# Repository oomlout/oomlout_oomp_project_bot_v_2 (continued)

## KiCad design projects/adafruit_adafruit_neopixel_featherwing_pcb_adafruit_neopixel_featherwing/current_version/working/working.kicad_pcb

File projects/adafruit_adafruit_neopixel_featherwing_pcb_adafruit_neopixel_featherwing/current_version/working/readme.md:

# adafruit_neopixel_featherwing_pcb
 
## summary 
* id: adafruit_adafruit_neopixel_featherwing_pcb_adafruit_neopixel_featherwing
* user: adafruit
* name: adafruit_neopixel_featherwing_pcb
* board: adafruit_neopixel_featherwing
* repo: https://github.com/adafruit/Adafruit-NeoPixel-FeatherWing-PCB

* src_file_repo_sch: 
* src_file_repo_sch_link: https://github.com/adafruit/Adafruit-NeoPixel-FeatherWing-PCB/tree/master/
* full details link: https://github.com/oomlout/oomlout_oomp_project_bot_v_2/tree/main/projects/adafruit_adafruit_neopixel_featherwing_pcb_adafruit_neopixel_featherwing/current_version/working  

## schematic  
  
[schematic (pdf)](working_schematic.pdf) 

## pcb  

[board (pdf)](working.pdf)  

## working_bom
| Id | Designator | Footprint | Quantity | Designation | Supplier and ref |  | None | 
| --- | --- | --- | --- | --- | --- | --- | --- | 
| 1 | LED6,LED19,LED32,LED26,LED23,LED8,LED9,LED12,LED11,LED28,LED2,LED31,LED25,LED18,LED21,LED5,LED24,LED20,LED16,LED29,LED1,LED4,LED14,LED27,LED13,LED10,LED15,LED17,LED30,LED3,LED22,LED7 | LED3535 | 32 | WS2812B3535 |  |  | [''] | 
| 2 | C3,C2,C1,C4,C5 | 0805-NO | 5 | 10uF |  |  | [''] | 
| 3 | JP3,JP1 | 1X01_ROUND | 2 |  |  |  | [''] | 
| 4 | FID3,FID1 | FIDUCIAL_1MM | 2 | FIDUCIAL" |  |  | [''] | 
| 5 | U$2 | PCBFEAT-REV-040 | 1 |  |  |  | [''] | 
| 6 | D1,D2 | SOD-123 | 2 | MBR120 |  |  | [''] | 
| 7 | IC2 | SOT23-5 | 1 | 74AHCT1G125DBV |  |  | [''] | 
| 8 | SW1 | BTN_KMR2_4.6X2.8 | 1 | KMR2 |  |  | [''] | 
| 9 | MS1 | FEATHERWING | 1 | FEATHERWING |  |  | [''] | 
| 10 | SJ10,SJ7,SJ2,SJ18,SJ11,SJ19,SJ9,SJ1,SJ5,SJ16,SJ12,SJ3,SJ17,SJ8,SJ14,SJ4,SJ15,SJ6,SJ13 | SOLDERJUMPER_ARROW_NOPASTE | 19 |  |  |  | [''] | 
| 11 | U$4 | ADAFRUIT_TEXT_20MM | 1 |  |  |  | [''] | 
| 12 | U$3 | FEATHERLOGO | 1 |  |  |  | [''] | 
| 13 | SJ20 | SOLDERJUMPER_CLOSEDWIRE | 1 |  |  |  | [''] | 

## bom_schematic
| Ref | Qnty | Value | Cmp name | Footprint | Description | Vendor | DNP | 
| --- | --- | --- | --- | --- | --- | --- | --- | 
| C1, C2, C3, C4, C5 | 5 | 10uF | CAP_CERAMIC0805-NOOUTLINE | working:0805-NO |  |  |  | 
| D1, D2 | 2 | MBR120 | DIODE-SCHOTTKYSOD-123 | working:SOD-123 |  |  |  | 
| FID1, FID3 | 2 | FIDUCIAL"" | FIDUCIAL{dblquote}{dblquote} | working:FIDUCIAL_1MM |  |  |  | 
| IC2 | 1 | 741G125DBV | 741G125DBV | working:SOT23-5 |  |  |  | 
| JP1, JP3 | 2 | HEADER-1X1ROUND | HEADER-1X1ROUND | working:1X01_ROUND |  |  |  | 
| LED1, LED2, LED3, LED4, LED5, LED6, LED7, LED8, LED9, LED10, LED11, LED12, LED13, LED14, LED15, LED16, LED17, LED18, LED19, LED20, LED21, LED22, LED23, LED24, LED25, LED26, LED27, LED28, LED29, LED30, LED31, LED32 | 32 | WS2812B3535 | WS2812B3535 | working:LED3535 |  |  |  | 
| MS1 | 1 | FEATHERWING | FEATHERWING | working:FEATHERWING |  |  |  | 
| SJ1, SJ2, SJ3, SJ4, SJ5, SJ6, SJ7, SJ8, SJ9, SJ10, SJ11, SJ12, SJ13, SJ14, SJ15, SJ16, SJ17, SJ18, SJ19 | 19 | SOLDERJUMPER | SOLDERJUMPER | working:SOLDERJUMPER_ARROW_NOPASTE |  |  |  | 
| SJ20 | 1 | SOLDERJUMPERCLOSED | SOLDERJUMPERCLOSED | working:SOLDERJUMPER_CLOSEDWIRE |  |  |  | 
| SW1 | 1 | KMR2 | SWITCH_TACT_SMT4.6X2.8 | working:BTN_KMR2_4.6X2.8 |  |  |  |

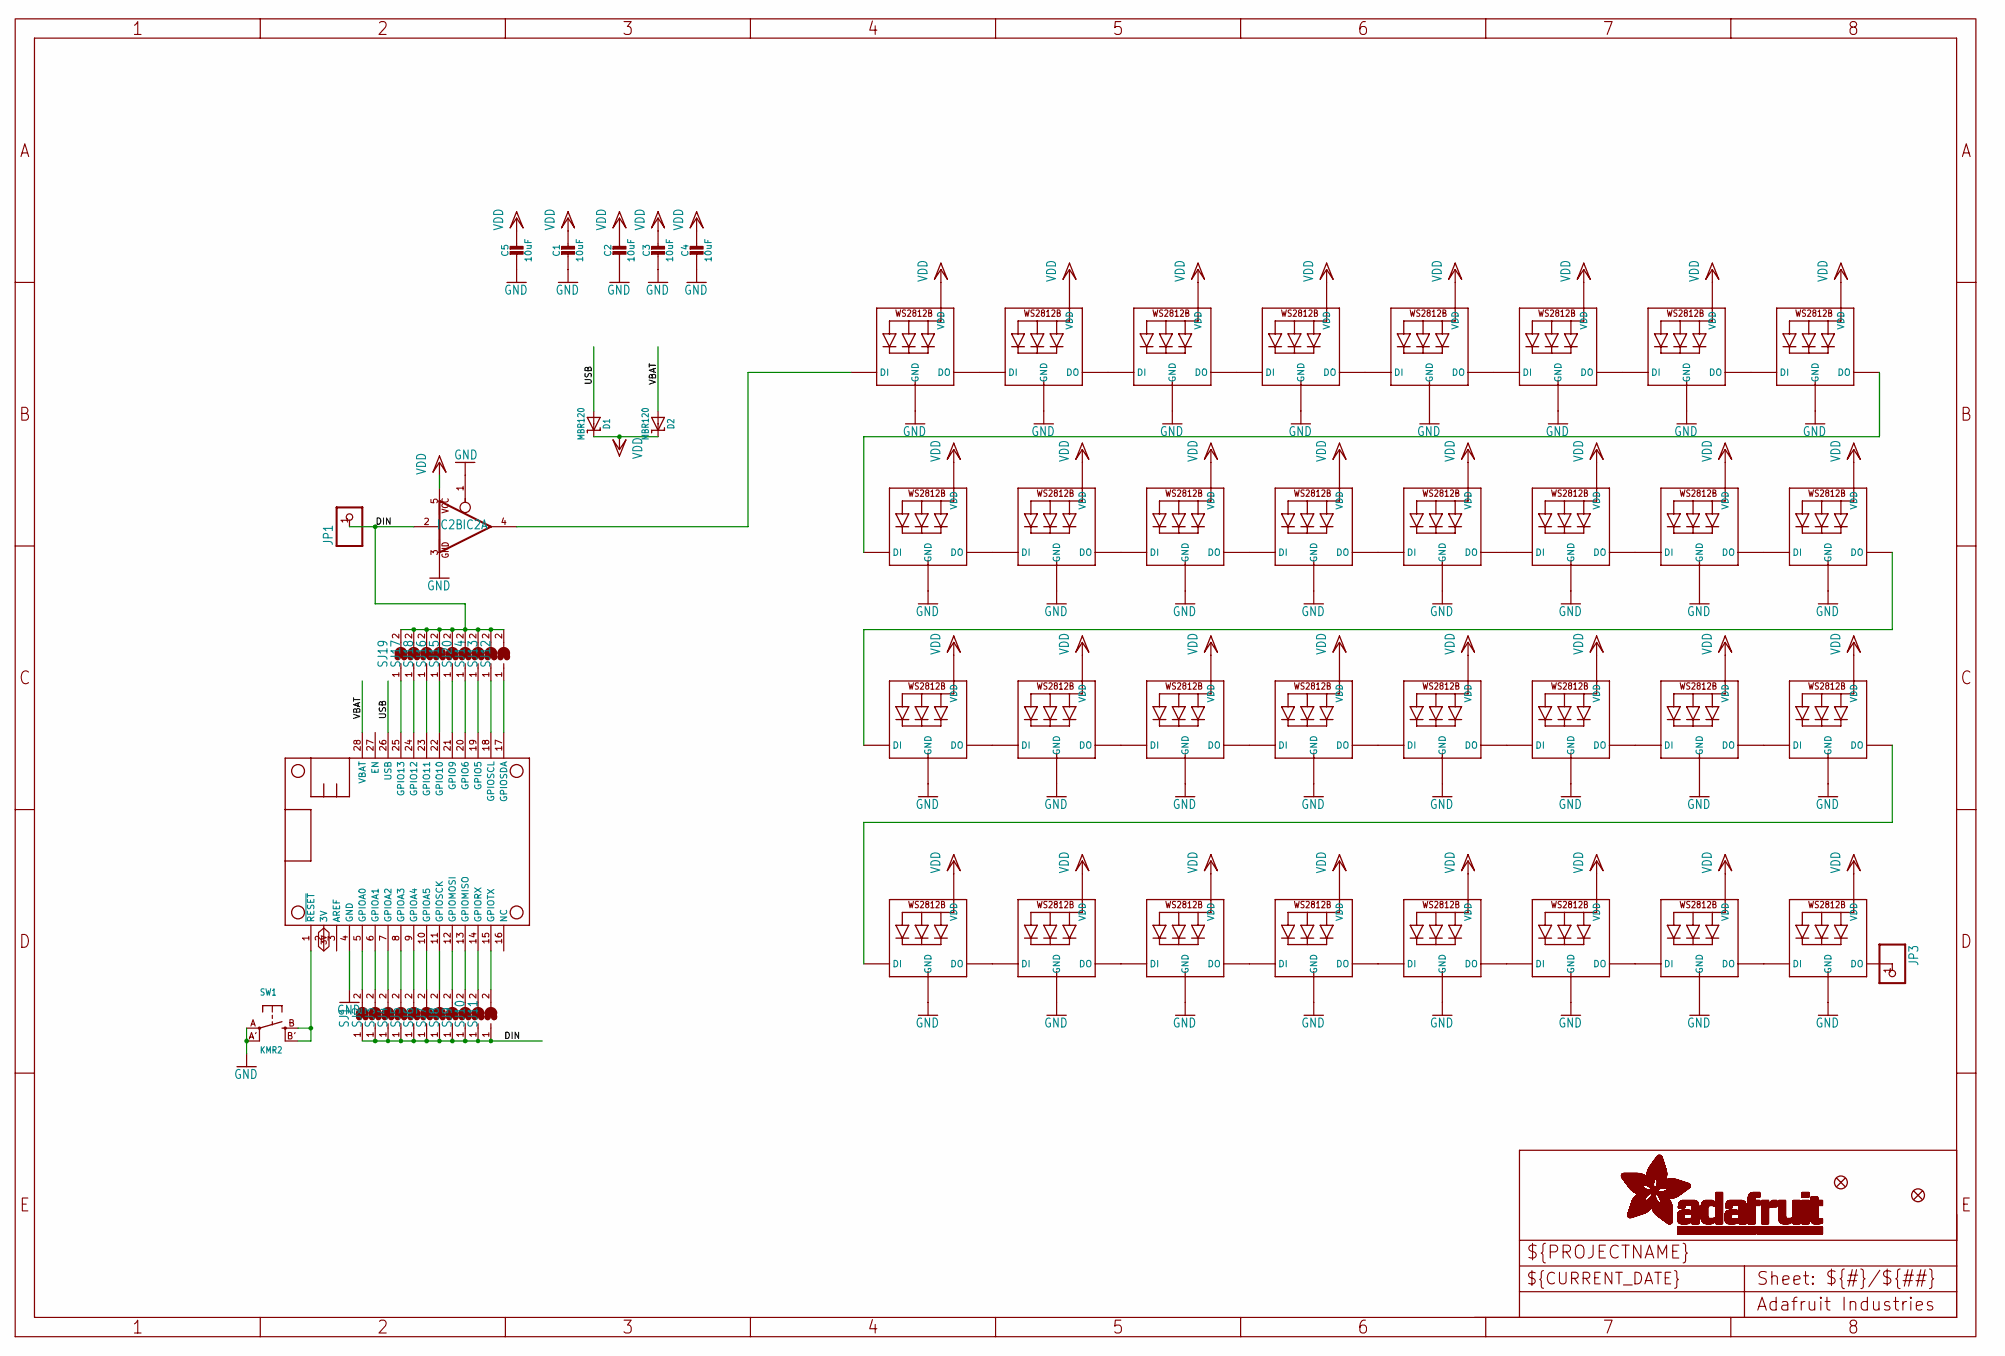
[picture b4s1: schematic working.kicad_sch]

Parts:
C1, C2, C3, C4, C5: 10uF; 0805-NO
D1, D2: MBR120; SOD-123
FID1, FID3: FIDUCIAL""; FIDUCIAL_1MM
IC2: 741G125DBV; SOT23-5
JP1, JP3: HEADER-1X1ROUND; 1X01_ROUND
LED1, LED2, LED3, LED4, LED5, LED6, LED7, LED8, LED9, LED10, LED11, LED12, LED13, LED14, LED15, LED16, LED17, LED18, LED19, LED20, LED21, LED22, LED23, LED24, LED25, LED26, LED27, LED28, LED29, LED30, LED31, LED32: WS2812B3535; LED3535
MS1: FEATHERWING
SJ1, SJ2, SJ3, SJ4, SJ5, SJ6, SJ7, SJ8, SJ9, SJ10, SJ11, SJ12, SJ13, SJ14, SJ15, SJ16, SJ17, SJ18, SJ19: SOLDERJUMPER; SOLDERJUMPER_ARROW_NOPASTE
SJ20: SOLDERJUMPERCLOSED; SOLDERJUMPER_CLOSEDWIRE
SW1: KMR2; BTN_KMR2_4.6X2.8

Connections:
D6: MS1.20 (GPIO6), SJ20.1
DIN: IC2.2 (I), JP1.1, SJ1.1, SJ2.1, SJ3.1, SJ4.1, SJ5.1, SJ6.1, SJ7.1, SJ8.1, SJ9.1, SJ10.1, SJ11.1, SJ12.2, SJ13.2, SJ14.2, SJ15.2, SJ16.2, SJ17.2, SJ18.2, SJ19.2, SJ20.2
GND: C1.2, C2.2, C3.2, C4.2, C5.2, IC2.1 (OE), IC2.3 (GND), LED1.4 (GND), LED2.4 (GND), LED3.4 (GND), LED4.4 (GND), LED5.4 (GND), LED6.4 (GND), LED7.4 (GND), LED8.4 (GND), LED9.4 (GND), LED10.4 (GND), LED11.4 (GND), LED12.4 (GND), LED13.4 (GND), LED14.4 (GND), LED15.4 (GND), LED16.4 (GND), LED17.4 (GND), LED18.4 (GND), LED19.4 (GND), LED20.4 (GND), LED21.4 (GND), LED22.4 (GND), LED23.4 (GND), LED24.4 (GND), LED25.4 (GND), LED26.4 (GND), LED27.4 (GND), LED28.4 (GND), LED29.4 (GND), LED30.4 (GND), LED31.4 (GND), LED32.4 (GND), MS1.4 (GND), SW1.A, SW1.A' (P1)
unnamed: LED19.3 (DO), LED20.1 (DI)
unnamed: LED20.3 (DO), LED21.1 (DI)
unnamed: MS1.25 (GPIO13), SJ19.1
unnamed: MS1.15 (GPIOTX), SJ11.2
unnamed: MS1.24 (GPIO12), SJ17.1
unnamed: MS1.14 (GPIORX), SJ10.2
unnamed: MS1.13 (GPIOMISO), SJ9.2
unnamed: MS1.12 (GPIOMOSI), SJ8.2
unnamed: MS1.11 (GPIOSCK), SJ7.2
unnamed: MS1.10 (GPIOA5), SJ6.2
unnamed: MS1.9 (GPIOA4), SJ5.2
unnamed: MS1.8 (GPIOA3), SJ4.2
unnamed: MS1.7 (GPIOA2), SJ3.2
unnamed: MS1.6 (GPIOA1), SJ2.2
unnamed: MS1.5 (GPIOA0), SJ1.2
unnamed: LED6.3 (DO), LED25.1 (DI)
unnamed: LED21.3 (DO), LED22.1 (DI)
unnamed: MS1.1 (~RESET), SW1.B (S), SW1.B' (S1)
unnamed: MS1.23 (GPIO11), SJ18.1
unnamed: MS1.22 (GPIO10), SJ16.1
unnamed: MS1.21 (GPIO9), SJ15.1
unnamed: IC2.4 (O), LED1.1 (DI)
unnamed: MS1.19 (GPIO5), SJ14.1
unnamed: MS1.18 (GPIOSCL), SJ13.1
unnamed: MS1.17 (GPIOSDA), SJ12.1
unnamed: LED1.3 (DO), LED2.1 (DI)
unnamed: LED2.3 (DO), LED3.1 (DI)
unnamed: LED3.3 (DO), LED4.1 (DI)
unnamed: LED4.3 (DO), LED5.1 (DI)
unnamed: LED5.3 (DO), LED6.1 (DI)
unnamed: LED7.3 (DO), LED8.1 (DI)
unnamed: LED8.3 (DO), LED9.1 (DI)
unnamed: LED9.3 (DO), LED10.1 (DI)
unnamed: LED10.3 (DO), LED11.1 (DI)
unnamed: LED11.3 (DO), LED12.1 (DI)
unnamed: LED13.3 (DO), LED14.1 (DI)
unnamed: LED14.3 (DO), LED15.1 (DI)
unnamed: LED15.3 (DO), LED16.1 (DI)
unnamed: LED16.3 (DO), LED17.1 (DI)
unnamed: LED17.3 (DO), LED18.1 (DI)
unnamed: LED12.3 (DO), LED27.1 (DI)
unnamed: LED7.1 (DI), LED26.3 (DO)
unnamed: LED22.3 (DO), LED23.1 (DI)
unnamed: LED23.3 (DO), LED24.1 (DI)
unnamed: LED19.1 (DI), LED30.3 (DO)
unnamed: LED24.3 (DO), LED31.1 (DI)
unnamed: LED25.3 (DO), LED26.1 (DI)
unnamed: LED27.3 (DO), LED28.1 (DI)
unnamed: LED18.3 (DO), LED29.1 (DI)
unnamed: LED29.3 (DO), LED30.1 (DI)
unnamed: LED31.3 (DO), LED32.1 (DI)
unnamed: JP3.1, LED32.3 (DO)
unnamed: LED13.1 (DI), LED28.3 (DO)
USB: D1.A, MS1.26 (USB)
VBAT: D2.A, MS1.28 (VBAT)
VDD: C1.1, C2.1, C3.1, C4.1, C5.1, D1.C, D2.C, IC2.5 (VCC), LED1.2 (VDD), LED2.2 (VDD), LED3.2 (VDD), LED4.2 (VDD), LED5.2 (VDD), LED6.2 (VDD), LED7.2 (VDD), LED8.2 (VDD), LED9.2 (VDD), LED10.2 (VDD), LED11.2 (VDD), LED12.2 (VDD), LED13.2 (VDD), LED14.2 (VDD), LED15.2 (VDD), LED16.2 (VDD), LED17.2 (VDD), LED18.2 (VDD), LED19.2 (VDD), LED20.2 (VDD), LED21.2 (VDD), LED22.2 (VDD), LED23.2 (VDD), LED24.2 (VDD), LED25.2 (VDD), LED26.2 (VDD), LED27.2 (VDD), LED28.2 (VDD), LED29.2 (VDD), LED30.2 (VDD), LED31.2 (VDD), LED32.2 (VDD)

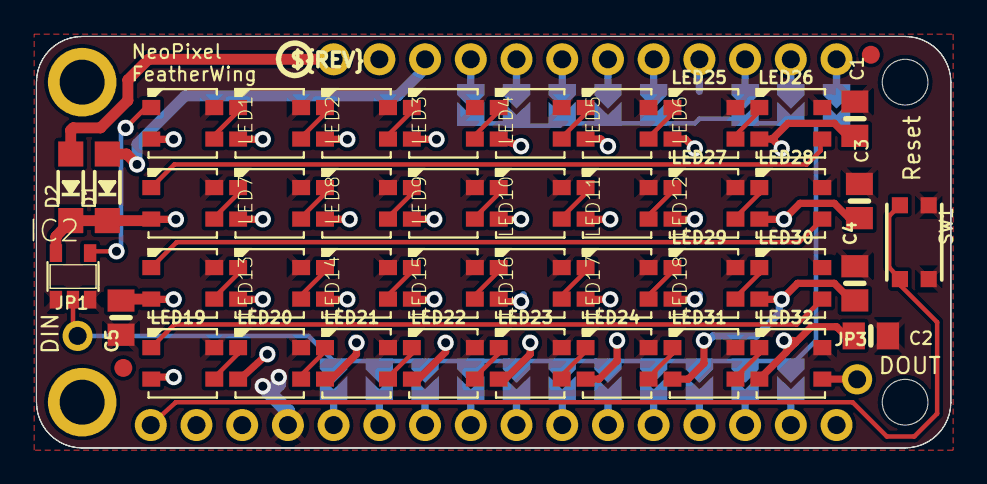
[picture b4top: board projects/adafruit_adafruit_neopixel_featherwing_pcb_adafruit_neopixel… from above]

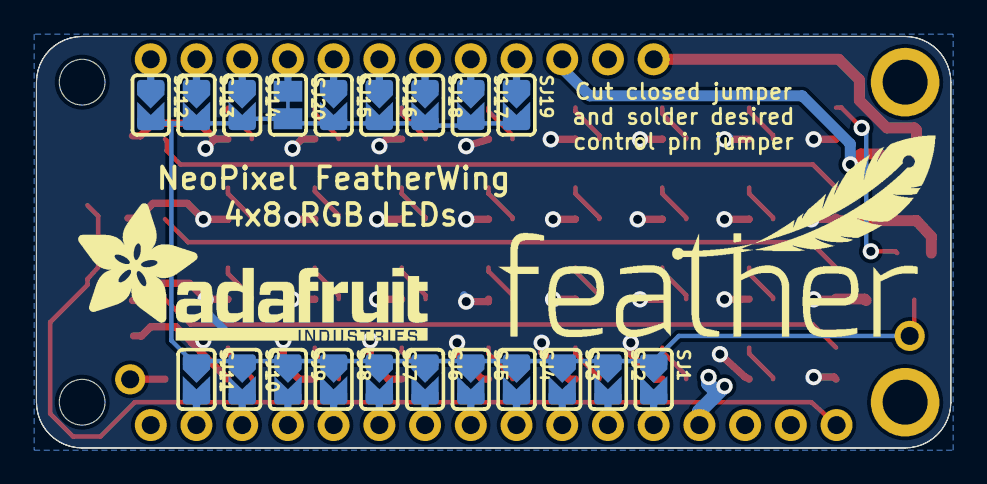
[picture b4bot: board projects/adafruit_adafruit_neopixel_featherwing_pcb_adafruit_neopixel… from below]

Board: 2 copper layers, 50.8 x 22.9 mm, 69 parts (22 on the bottom side), 59 nets.

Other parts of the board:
U$2: PCBFEAT-REV-040
U$3: FEATHERLOGO
U$4: ADAFRUIT_TEXT_20MM

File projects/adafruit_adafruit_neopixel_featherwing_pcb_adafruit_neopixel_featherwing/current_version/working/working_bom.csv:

"Id";"Designator";"Footprint";"Quantity";"Designation";"Supplier and ref";
1;"LED6,LED19,LED32,LED26,LED23,LED8,LED9,LED12,LED11,LED28,LED2,LED31,LED25,LED18,LED21,LED5,LED24,LED20,LED16,LED29,LED1,LED4,LED14,LED27,LED13,LED10,LED15,LED17,LED30,LED3,LED22,LED7";"LED3535";32;"WS2812B3535";;;
2;"C3,C2,C1,C4,C5";"0805-NO";5;"10uF";;;
3;"JP3,JP1";"1X01_ROUND";2;"";;;
4;"FID3,FID1";"FIDUCIAL_1MM";2;"FIDUCIAL""";;;
5;"U$2";"PCBFEAT-REV-040";1;"";;;
6;"D1,D2";"SOD-123";2;"MBR120";;;
7;"IC2";"SOT23-5";1;"74AHCT1G125DBV";;;
8;"SW1";"BTN_KMR2_4.6X2.8";1;"KMR2";;;
9;"MS1";"FEATHERWING";1;"FEATHERWING";;;
10;"SJ10,SJ7,SJ2,SJ18,SJ11,SJ19,SJ9,SJ1,SJ5,SJ16,SJ12,SJ3,SJ17,SJ8,SJ14,SJ4,SJ15,SJ6,SJ13";"SOLDERJUMPER_ARROW_NOPASTE";19;"";;;
11;"U$4";"ADAFRUIT_TEXT_20MM";1;"";;;
12;"U$3";"FEATHERLOGO";1;"";;;
13;"SJ20";"SOLDERJUMPER_CLOSEDWIRE";1;"";;;

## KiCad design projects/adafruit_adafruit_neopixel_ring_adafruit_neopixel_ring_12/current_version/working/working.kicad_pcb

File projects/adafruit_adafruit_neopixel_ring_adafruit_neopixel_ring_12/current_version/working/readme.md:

# adafruit_neopixel_ring
 
## summary 
* id: adafruit_adafruit_neopixel_ring_adafruit_neopixel_ring_12
* user: adafruit
* name: adafruit_neopixel_ring
* board: adafruit_neopixel_ring_12
* repo: https://github.com/adafruit/Adafruit-NeoPixel-Ring

* src_file_repo_sch: 
* src_file_repo_sch_link: https://github.com/adafruit/Adafruit-NeoPixel-Ring/tree/master/
* full details link: https://github.com/oomlout/oomlout_oomp_project_bot_v_2/tree/main/projects/adafruit_adafruit_neopixel_ring_adafruit_neopixel_ring_12/current_version/working  

## schematic  
  
[schematic (pdf)](working_schematic.pdf) 

## pcb  

[board (pdf)](working.pdf)  

## working_bom
| Id | Designator | Footprint | Quantity | Designation | Supplier and ref |  | None | 
| --- | --- | --- | --- | --- | --- | --- | --- | 
| 1 | LED5,LED6,LED7,LED12,LED4,LED1,LED11,LED8,LED3,LED9,LED10,LED2 | WS28115050 | 12 | WS28115050 |  |  | [''] | 
| 2 | JP2,JP1,JP3,JP4 | 1X01-CLEANBIG | 4 |  |  |  | [''] | 
| 3 | C4,C2,C6,C10,C9,C3,C8,C12 | C0603 | 8 |  |  |  | [''] | 
| 4 | U$1,U$2 | GUIDE-STAR-12 | 2 |  |  |  | [''] | 
| 5 | U$3 | ADAFRUIT_5MM | 1 |  |  |  | [''] | 

## bom_schematic
| Ref | Qnty | Value | Cmp name | Footprint | Description | Vendor | DNP | 
| --- | --- | --- | --- | --- | --- | --- | --- | 
| C2, C3, C4, C6, C8, C9, C10, C12 | 8 | C-EUC0603 | C-EUC0603 | working:C0603 |  |  |  | 
| JP1, JP2, JP3, JP4 | 4 | PINHD-1X1CB | PINHD-1X1CB | working:1X01-CLEANBIG |  |  |  | 
| LED1, LED2, LED3, LED4, LED5, LED6, LED7, LED8, LED9, LED10, LED11, LED12 | 12 | WS28115050 | WS28115050 | working:WS28115050 |  |  |  |

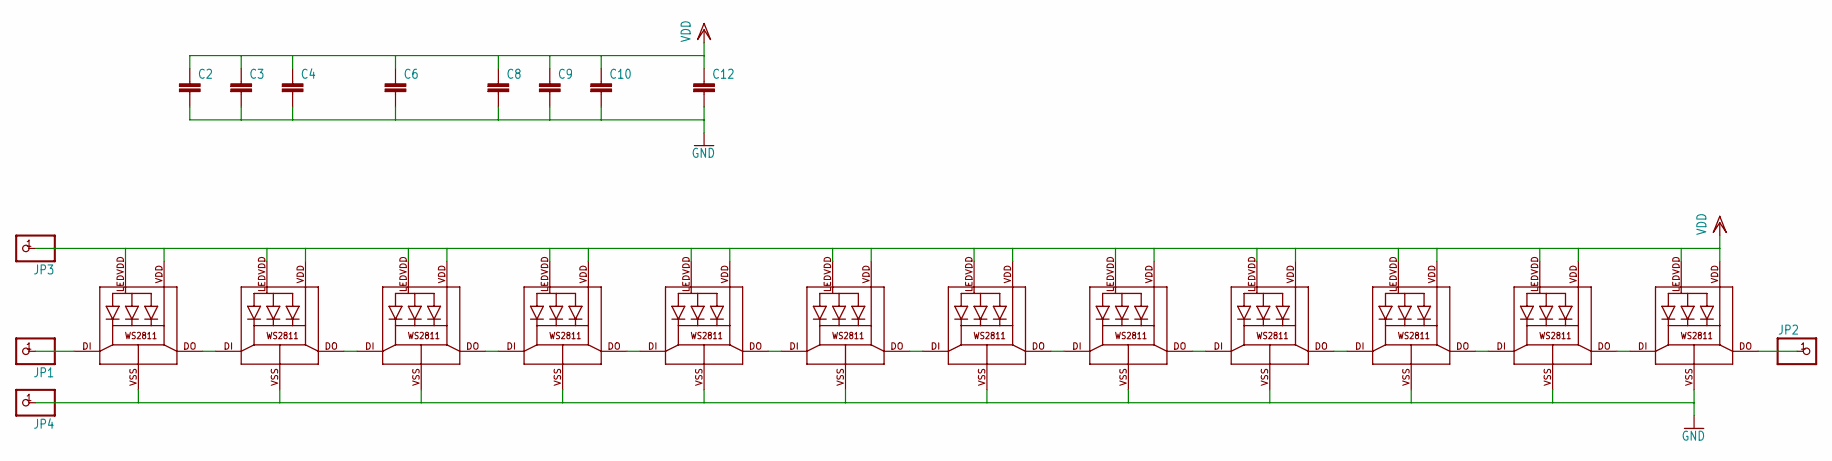
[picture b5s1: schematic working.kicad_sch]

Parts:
C2, C3, C4, C6, C8, C9, C10, C12: C-EUC0603; C0603
JP1, JP2, JP3, JP4: PINHD-1X1CB; 1X01-CLEANBIG
LED1, LED2, LED3, LED4, LED5, LED6, LED7, LED8, LED9, LED10, LED11, LED12: WS28115050

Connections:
GND: C2.2, C3.2, C4.2, C6.2, C8.2, C9.2, C10.2, C12.2, JP4.1, LED1.VSS (GND), LED2.VSS (GND), LED3.VSS (GND), LED4.VSS (GND), LED5.VSS (GND), LED6.VSS (GND), LED7.VSS (GND), LED8.VSS (GND), LED9.VSS (GND), LED10.VSS (GND), LED11.VSS (GND), LED12.VSS (GND)
unnamed: LED1.DO, LED2.DI
unnamed: LED2.DO, LED3.DI
unnamed: LED3.DO, LED4.DI
unnamed: LED4.DO, LED5.DI
unnamed: LED5.DO, LED6.DI
unnamed: LED6.DO, LED7.DI
unnamed: LED7.DO, LED8.DI
unnamed: LED8.DO, LED9.DI
unnamed: LED9.DO, LED10.DI
unnamed: LED10.DO, LED11.DI
unnamed: LED11.DO, LED12.DI
unnamed: JP1.1, LED1.DI
unnamed: JP2.1, LED12.DO
VDD: C2.1, C3.1, C4.1, C6.1, C8.1, C9.1, C10.1, C12.1, JP3.1, LED1.LEDVDD, LED1.VDD, LED2.LEDVDD, LED2.VDD, LED3.LEDVDD, LED3.VDD, LED4.LEDVDD, LED4.VDD, LED5.LEDVDD, LED5.VDD, LED6.LEDVDD, LED6.VDD, LED7.LEDVDD, LED7.VDD, LED8.LEDVDD, LED8.VDD, LED9.LEDVDD, LED9.VDD, LED10.LEDVDD, LED10.VDD, LED11.LEDVDD, LED11.VDD, LED12.LEDVDD, LED12.VDD

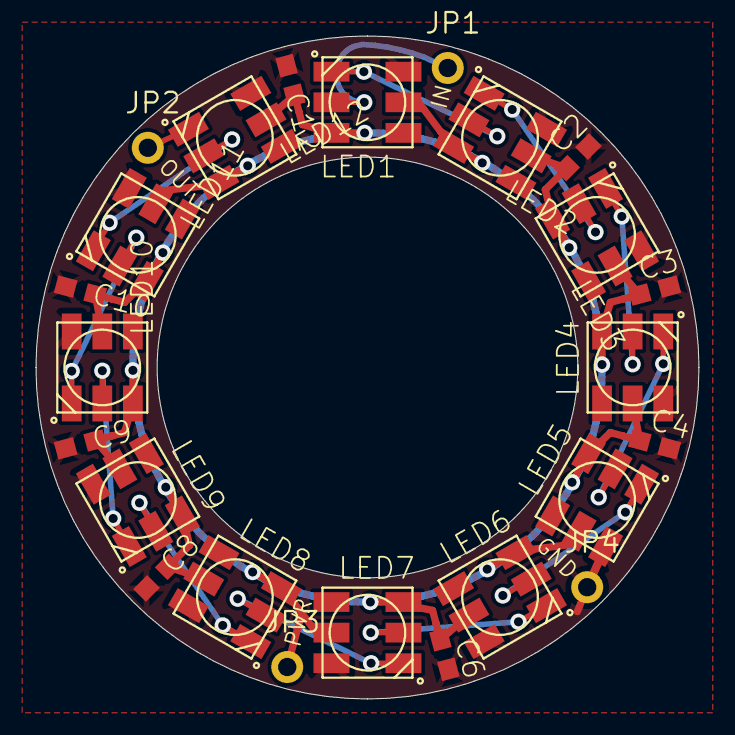
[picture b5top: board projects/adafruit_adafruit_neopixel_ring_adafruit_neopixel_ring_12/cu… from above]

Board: 2 copper layers, 36.8 x 36.8 mm, 27 parts (1 on the bottom side), 15 nets.

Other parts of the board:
U$1, U$2: GUIDE-STAR-12
U$3: ADAFRUIT_5MM
